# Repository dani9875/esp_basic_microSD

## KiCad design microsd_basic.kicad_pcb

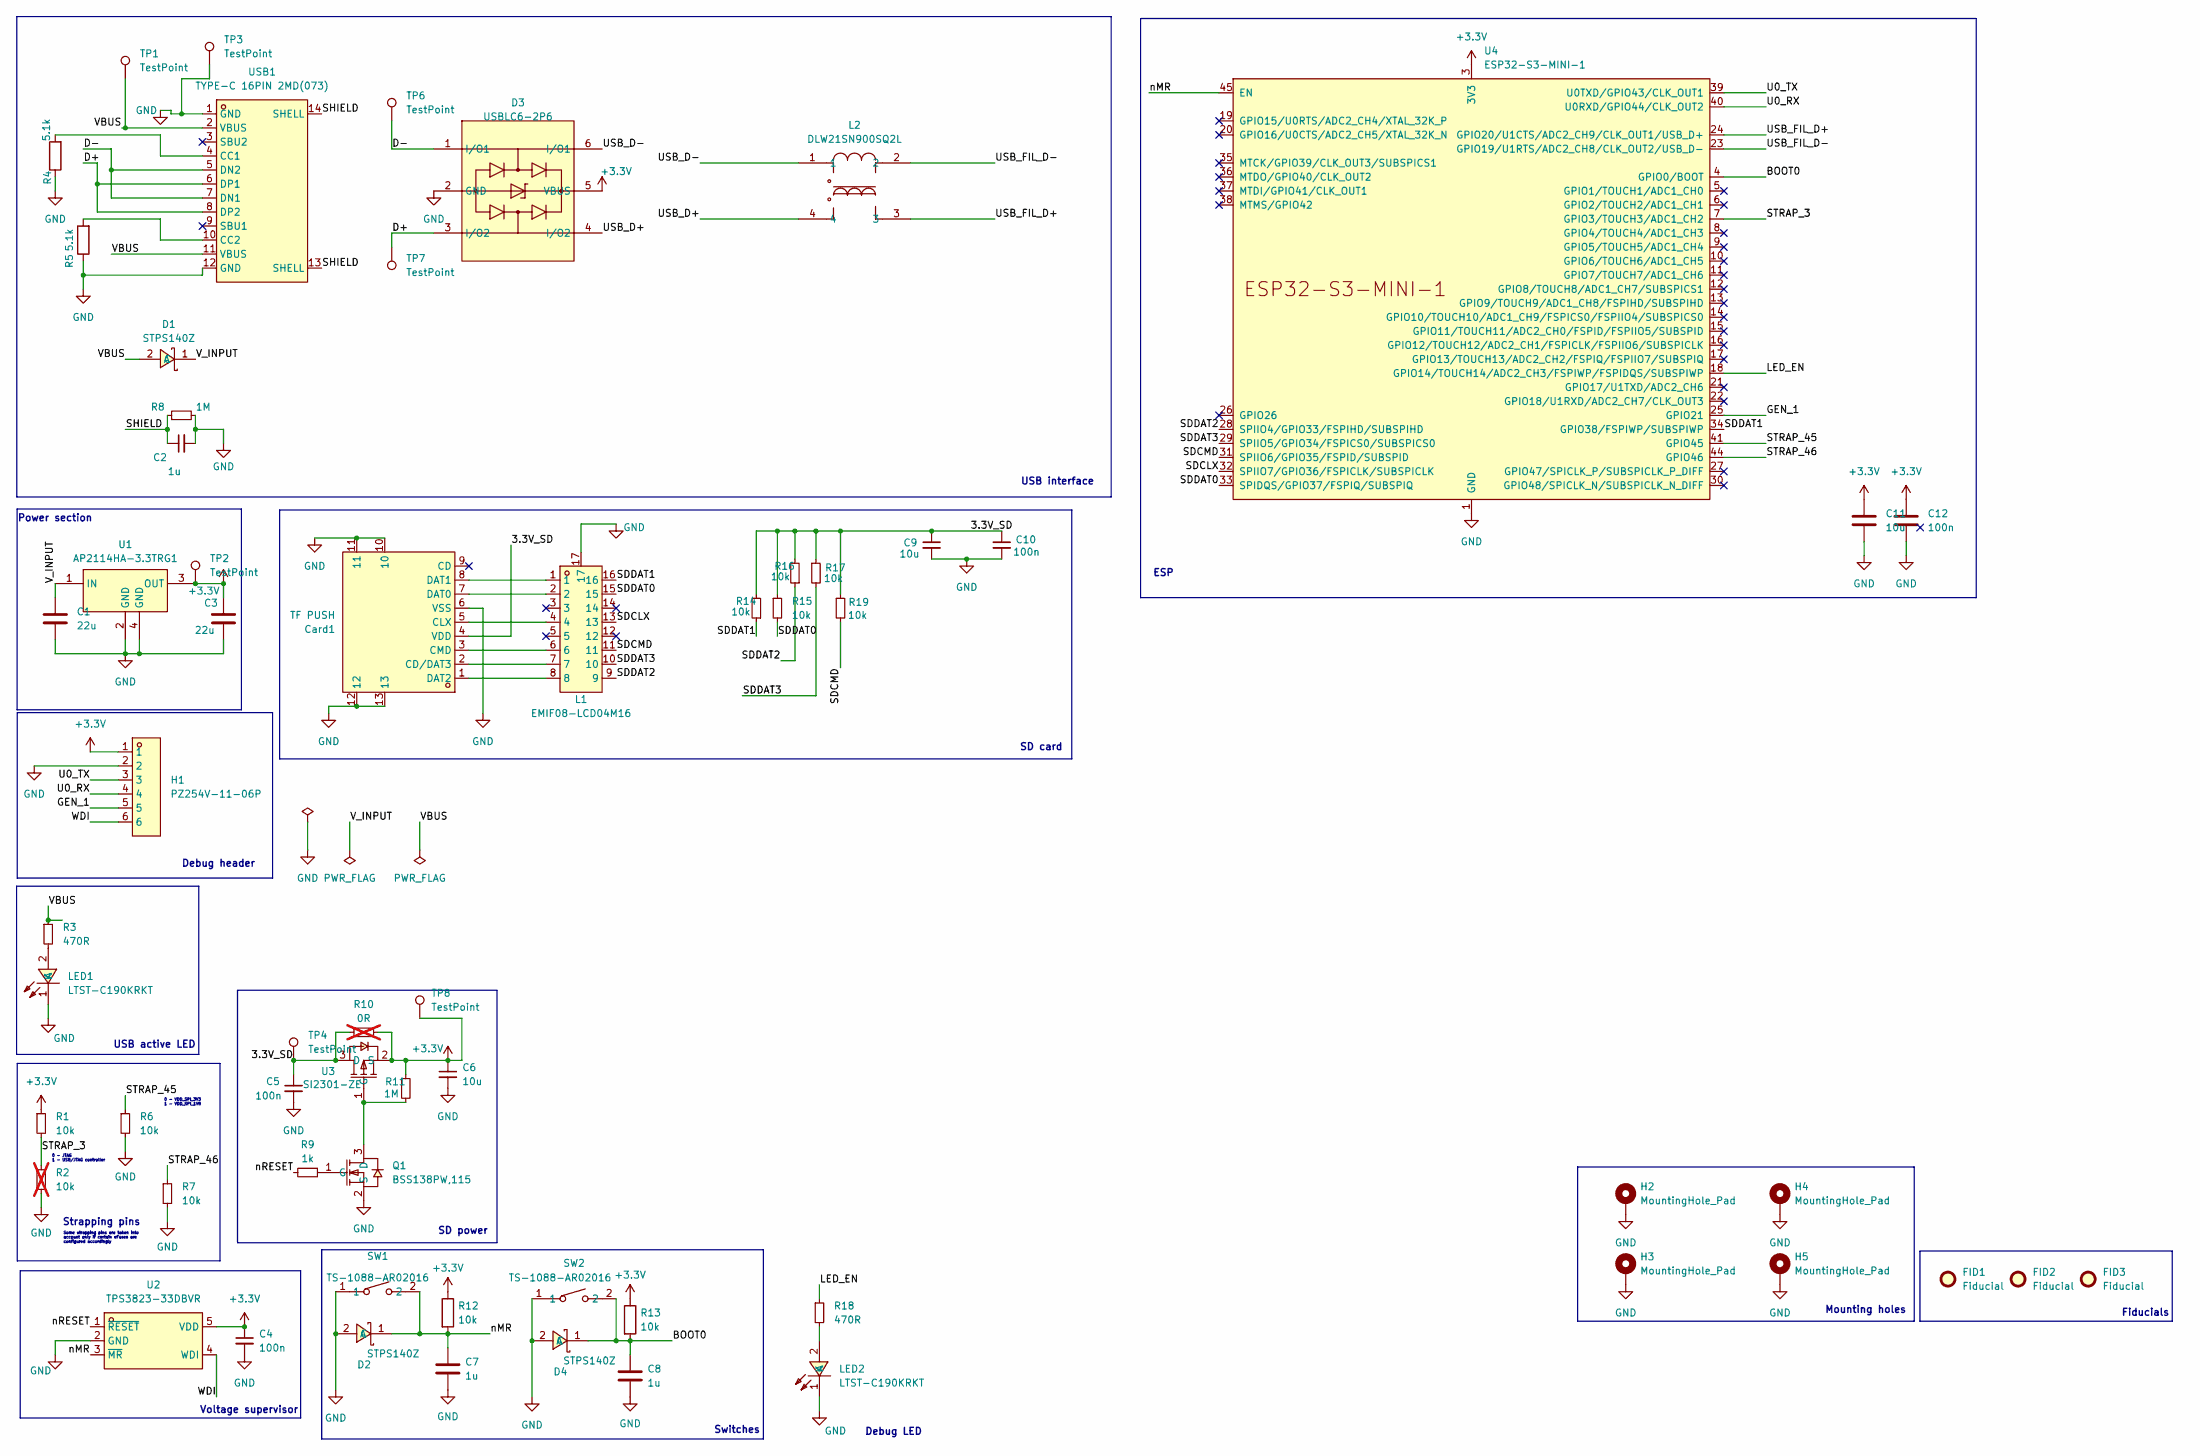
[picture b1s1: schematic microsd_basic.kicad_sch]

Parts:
C1, C3: 22u; C_0805_2012Metric
C2, C7, C8: 1u; C_0805_2012Metric
C4, C5, C10, C12: 100n; C_0805_2012Metric
C6, C9, C11: 10u; C_0805_2012Metric
Card1: TF PUSH; [MICRO_SD_PUSH]SHOU HAN TF PUSH; LCSC Part C393941
D1, D2, D4: STPS140Z; SOD-123_L2.8-W1.8-LS3.7-RD; LCSC Part C155662
D3: USBLC6-2P6; SOT-666-6_L1.6-W1.2-P0.50-LS1.6-BR; LCSC Part C15999
FID1, FID2, FID3: Fiducial; Fiducial_0.5mm_Mask1mm
H1: PZ254V-11-06P; [6P_HEADER_STR]XFCN PZ254V-11-06P; LCSC Part C492405
H2, H3, H4, H5: MountingHole_Pad; MountingHole_2.2mm_M2_DIN965_Pad
L1: EMIF08-LCD04M16; [EMI_FILTER_W_ESD_PROT]STMicroelectronics EMIF08-LCD04M16; LCSC Part C2802060
L2: DLW21SN900SQ2L; FILTER-SMD_4P-L2.0-W1.2-BL_DLW21H; LCSC Part C97856
LED1, LED2: LTST-C190KRKT; [LED]Lite-On LTST-C190KRKT; LCSC Part C94869
Q1: BSS138PW,115; [NMOS]Nexperia BSS138PW,115; LCSC Part C193366
R1, R6, R7, R12, R13, R14, R15, R16, R17, R19: 10k; R_0805_2012Metric
R2: 10k; R_0805_2012Metric; not fitted
R3, R18: 470R; R_0805_2012Metric
R4, R5: 5.1k; R_0805_2012Metric
R8, R11: 1M; R_0805_2012Metric
R9: 1k; R_0805_2012Metric
R10: 0R; R_0805_2012Metric; not fitted
SW1, SW2: TS-1088-AR02016; [TACTILE_SWITCH]XUNPU TS-1088-AR02016; LCSC Part C720477
TP1, TP2, TP3, TP4, TP6, TP7, TP8: TestPoint; TestPoint_Pad_D1.0mm
U1: AP2114HA-3.3TRG1; [LDO]Diodes Incorporated AP2114HA-3.3TRG1; LCSC Part C460314
U2: TPS3823-33DBVR; [VOLTAGE_SUPERVISOR]Texas Instruments TPS3823-33DBVR; LCSC Part C7719
U3: SI2301-ZE; [POWER_PMOS]HXY MOSFET SI2301-ZE; LCSC Part C5261052
U4: ESP32-S3-MINI-1
USB1: TYPE-C 16PIN 2MD(073); USB-C-SMD_TYPE-C-6PIN-2MD-073; LCSC Part C2765186

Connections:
+3.3V: C3.1, C4.1, C6.1, C11.1, C12.1, D3.5 (VBUS), H1.1, R1.1, R10.2, R11.1, R12.1, R13.1, TP2.1, TP8.1, U1.3 (OUT), U2.5 (VDD), U3.2 (S), U4.3 (3V3); also elsewhere on the board
/3.3V_SD: C5.1, C9.1, C10.1, Card1.4 (VDD), R10.1, R14.2, R15.1, R16.2, R17.1, R19.1, TP4.1, U3.3 (D); also elsewhere on the board
/BOOT0: C8.1, D4.1 (C), R13.2, SW2.2, U4.4 (GPIO0/BOOT)
/D+: D3.3 (I/O2), TP7.1, USB1.6 (DP1), USB1.8 (DP2); also elsewhere on the board
/D-: D3.1 (I/O1), TP6.1, USB1.5 (DN2), USB1.7 (DN1); also elsewhere on the board
/GEN_1: H1.5, U4.25 (GPIO21)
/LED_EN: R18.1, U4.18 (GPIO14/TOUCH14/ADC2_CH3/FSPIWP/FSPIDQS/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)
/SDCLX: L1.13, U4.32 (SPIIO7/GPIO36/FSPICLK/SUBSPICLK)
/SDCMD: L1.11, R19.2, U4.31 (SPIIO6/GPIO35/FSPID/SUBSPID)
/SDDAT0: L1.15, R15.2, U4.33 (SPIDQS/GPIO37/FSPIQ/SUBSPIQ)
/SDDAT1: L1.16, R14.1, U4.34 (GPIO38/FSPIWP/SUBSPIWP)
/SDDAT2: L1.9, R16.1, U4.28 (SPIIO4/GPIO33/FSPIHD/SUBSPIHD)
/SDDAT3: L1.10, R17.2, U4.29 (SPIIO5/GPIO34/FSPICS0/SUBSPICS0)
/SHIELD: C2.1, R8.1, USB1.13 (SHELL), USB1.14 (SHELL)
/STRAP_3: R1.2, R2.1, U4.7 (GPIO3/TOUCH3/ADC1_CH2)
/STRAP_45: R6.1, U4.41 (GPIO45)
/STRAP_46: R7.1, U4.44 (GPIO46)
/U0_RX: H1.4, U4.40 (U0RXD/GPIO44/CLK_OUT2)
/U0_TX: H1.3, U4.39 (U0TXD/GPIO43/CLK_OUT1)
/USB_D+: D3.4 (I/O2), L2.4
/USB_D-: D3.6 (I/O1), L2.1
/USB_FIL_D+: L2.3, U4.24 (GPIO20/U1CTS/ADC2_CH9/CLK_OUT1/USB_D+)
/USB_FIL_D-: L2.2, U4.23 (GPIO19/U1RTS/ADC2_CH8/CLK_OUT2/USB_D-)
/VBUS: D1.2 (A), R3.1, TP1.1, USB1.2 (VBUS), USB1.11 (VBUS); also elsewhere on the board
/V_INPUT: C1.1, D1.1 (C), U1.1 (IN)
/WDI: H1.6, U2.4 (WDI)
/nMR: C7.1, D2.1 (C), R12.2, SW1.2, U2.3 (~MR), U4.45 (EN)
/nRESET: R9.2, U2.1 (~RESET)
GND: C1.2, C2.2, C3.2, C4.2, C5.2, C6.2, C7.2, C8.2, C9.2, C10.2, C11.2, C12.2, Card1.6 (VSS), Card1.10, Card1.11, Card1.12, Card1.13, D2.2 (A), D3.2 (GND), D4.2 (A), H1.2, H2.1, H3.1, H4.1, H5.1, L1.17, LED1.1 (K), LED2.1 (K), Q1.2 (S), R2.2, R4.1, R5.1, R6.2, R7.2, R8.2, SW1.1, SW2.1, TP3.1, U1.2 (GND), U1.4 (GND), U2.2 (GND), U4.1 (GND), U4.2 (GND), U4.42 (GND), U4.43 (GND), U4.46 (GND), U4.47 (GND), U4.48 (GND), U4.49 (GND), U4.50 (GND), U4.51 (GND), U4.52 (GND), U4.53 (GND), U4.54 (GND), U4.55 (GND), U4.56 (GND), U4.57 (GND), U4.58 (GND), U4.59 (GND), U4.60 (GND), U4.61 (GND), U4.62 (GND), U4.63 (GND), U4.64 (GND), U4.65 (GND), USB1.1 (GND), USB1.12 (GND); also elsewhere on the board
unnamed: Card1.2 (CD/DAT3), L1.7
unnamed: Card1.5 (CLX), L1.4
unnamed: Card1.3 (CMD), L1.6
unnamed: Card1.7 (DAT0), L1.2
unnamed: Card1.8 (DAT1), L1.1
unnamed: Card1.1 (DAT2), L1.8
unnamed: LED1.2 (A), R3.2
unnamed: LED2.2 (A), R18.2
unnamed: Q1.3 (D), R11.2, U3.1 (G)
unnamed: Q1.1 (G), R9.1
unnamed: R4.2, USB1.4 (CC1)
unnamed: R5.2, USB1.10 (CC2)

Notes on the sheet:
SD power
Debug LED
Strapping pins
0 - VDD_SPI_3V3 1 - VDD_SPI_1V8
Some strapping pins are taken into account only if certain eFuses are configured accordingly
Debug header
Fiducials
SD card
Switches
USB active LED
ESP
Voltage supervisor
USB interface
Power section
0 - JTAG 1 - USB/JTAG controller
Mounting holes

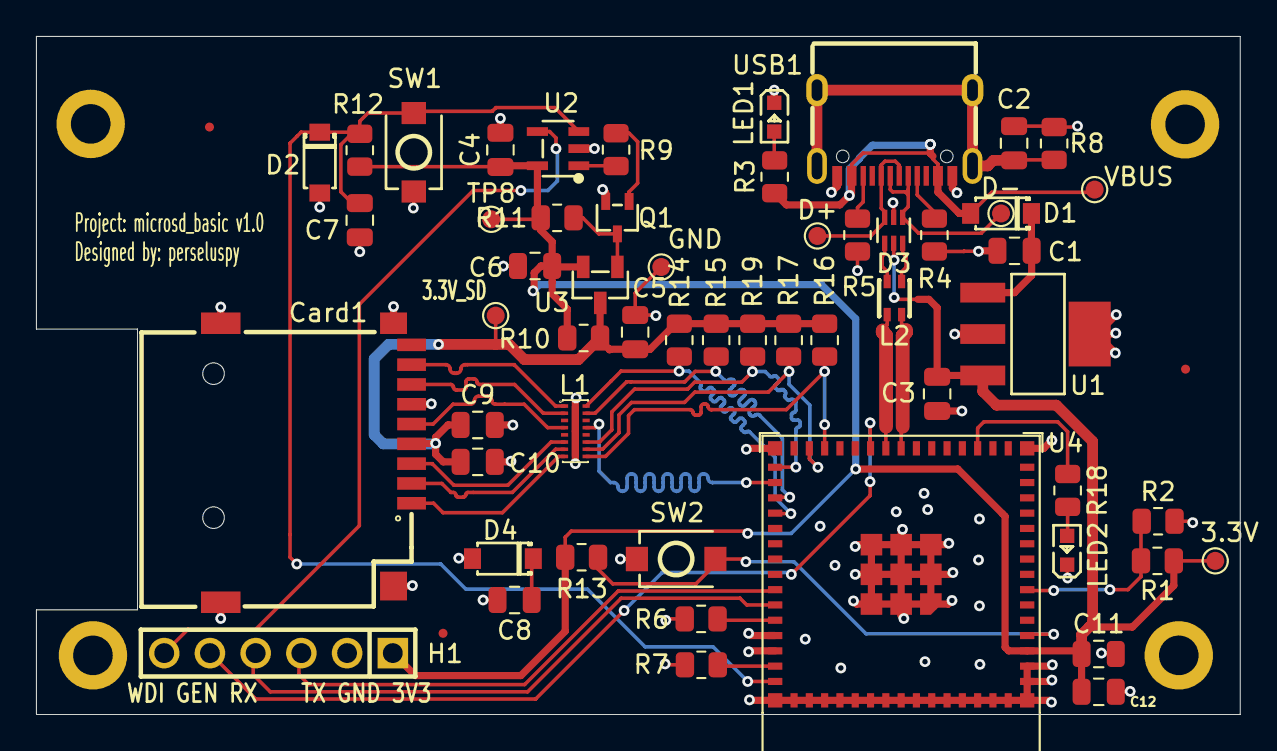
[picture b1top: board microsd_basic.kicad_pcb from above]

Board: 2 copper layers, 66.9 x 37.7 mm, 63 parts (0 on the bottom side), 41 nets.

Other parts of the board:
3.3V, 3.3V_SD: TestPoint; TestPoint_Pad_D1.0mm
D+: TestPoint; TestPoint_Pad_D1.0mm
D-: TestPoint; TestPoint_Pad_D1.0mm
GND: TestPoint; TestPoint_Pad_D1.0mm
VBUS: TestPoint; TestPoint_Pad_D1.0mm

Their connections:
+3.3V: 3.3V.1; also elsewhere on the board
/3.3V_SD: 3.3V_SD.1; also elsewhere on the board
/D+: D+.1; also elsewhere on the board
/D-: D-.1; also elsewhere on the board
/VBUS: VBUS.1; also elsewhere on the board
GND: GND.1; also elsewhere on the board

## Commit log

2024-05-19 Init HW files
2024-05-26 Final v1.0
